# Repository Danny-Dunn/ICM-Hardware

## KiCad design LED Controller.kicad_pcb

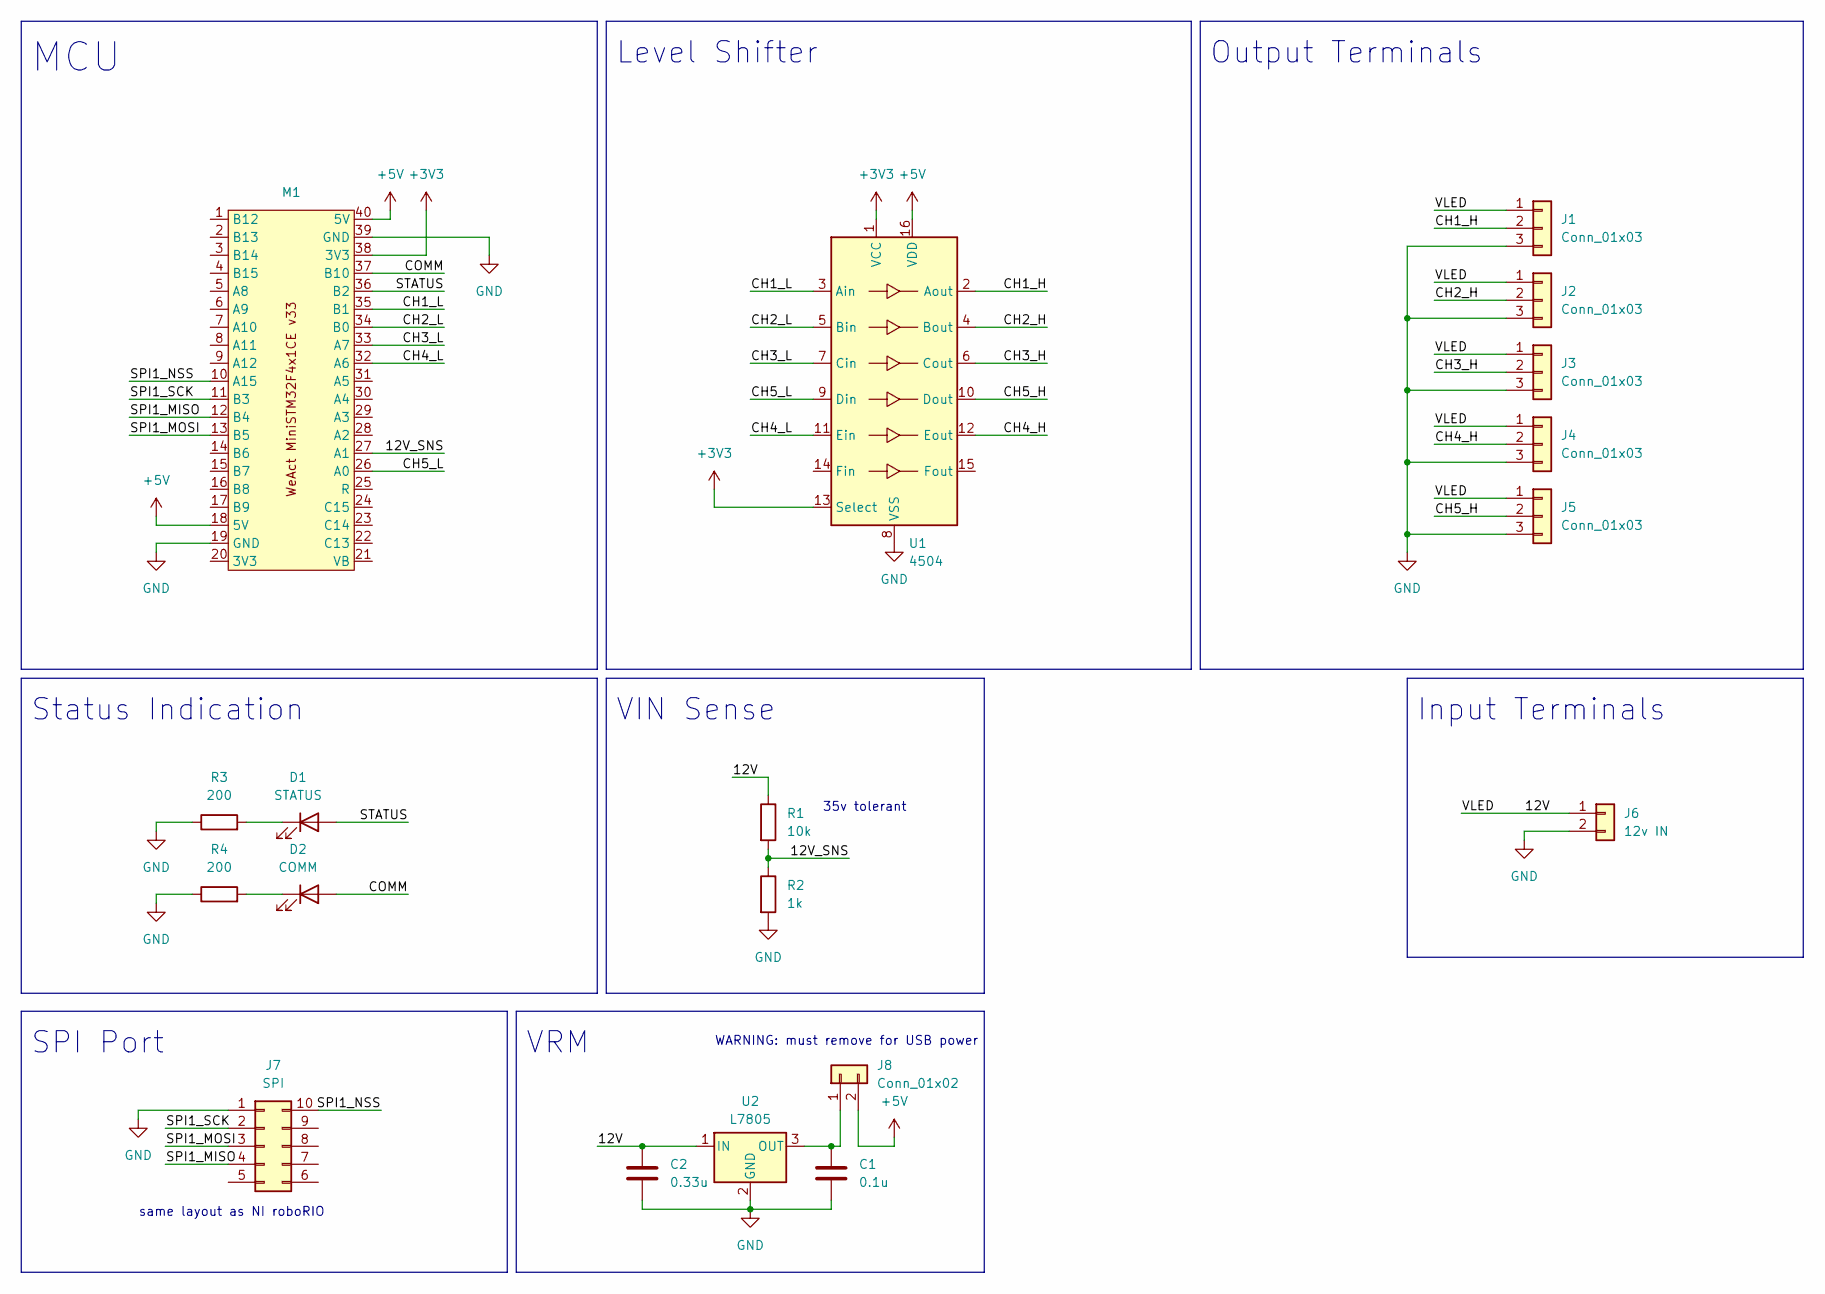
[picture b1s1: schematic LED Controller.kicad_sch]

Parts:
C1: 0.1u; CP_Radial_D5.0mm_P2.00mm
C2: 0.33u; CP_Radial_D4.0mm_P1.50mm
D1: STATUS; LED_0805_2012Metric
D2: COMM; LED_0805_2012Metric
J1, J2, J3, J4, J5: Conn_01x03; PinHeader_1x03_P2.54mm_Vertical
J6: 12v IN; TerminalBlock_WAGO_804-102_1x02_P5.00mm_45Degree
J7: SPI; PinHeader_2x05_P2.54mm_Vertical
J8: Conn_01x02; PinHeader_1x02_P2.54mm_Vertical
M1: MiniSTM32F4x1CE
R1: 10k; R_0805_2012Metric
R2: 1k; R_0805_2012Metric
R3, R4: 200; R_0805_2012Metric
U1: 4504; DIP-16_W7.62mm
U2: L7805; TO-220-3_Horizontal_TabDown

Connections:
+3V3: M1.38 (3V3), U1.1 (VCC), U1.13 (Select)
+5V: J8.2, M1.18 (5V), M1.40 (5V), U1.16 (VDD)
/12V: C2.1, J1.1, J2.1, J3.1, J4.1, J5.1, J6.1, R1.1, U2.1 (IN)
/12V_SNS: M1.27 (A1), R1.2, R2.1
/CH1_H: J1.2, U1.2 (Aout)
/CH1_L: M1.35 (B1), U1.3 (Ain)
/CH2_H: J2.2, U1.4 (Bout)
/CH2_L: M1.34 (B0), U1.5 (Bin)
/CH3_H: J3.2, U1.6 (Cout)
/CH3_L: M1.33 (A7), U1.7 (Cin)
/CH4_H: J4.2, U1.12 (Eout)
/CH4_L: M1.32 (A6), U1.11 (Ein)
/CH5_H: J5.2, U1.10 (Dout)
/CH5_L: M1.26 (A0), U1.9 (Din)
/COMM: D2.2 (A), M1.37 (B10)
/SPI1_MISO: J7.4, M1.12 (B4)
/SPI1_MOSI: J7.3, M1.13 (B5)
/SPI1_NSS: J7.10, M1.10 (A15)
/SPI1_SCK: J7.2, M1.11 (B3)
/STATUS: D1.2 (A), M1.36 (B2)
GND: C1.2, C2.2, J1.3, J2.3, J3.3, J4.3, J5.3, J6.2, J7.1, M1.19 (GND), M1.39 (GND), R2.2, R3.1, R4.1, U1.8 (VSS), U2.2 (GND)
unnamed: D1.1 (K), R3.2
unnamed: D2.1 (K), R4.2
unnamed: C1.1, J8.1, U2.3 (OUT)

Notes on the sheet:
Input Terminals
Level Shifter
Status Indication
same layout as NI roboRIO
VRM
SPI Port
WARNING: must remove for USB power
35v tolerant
MCU
Output Terminals
VIN Sense

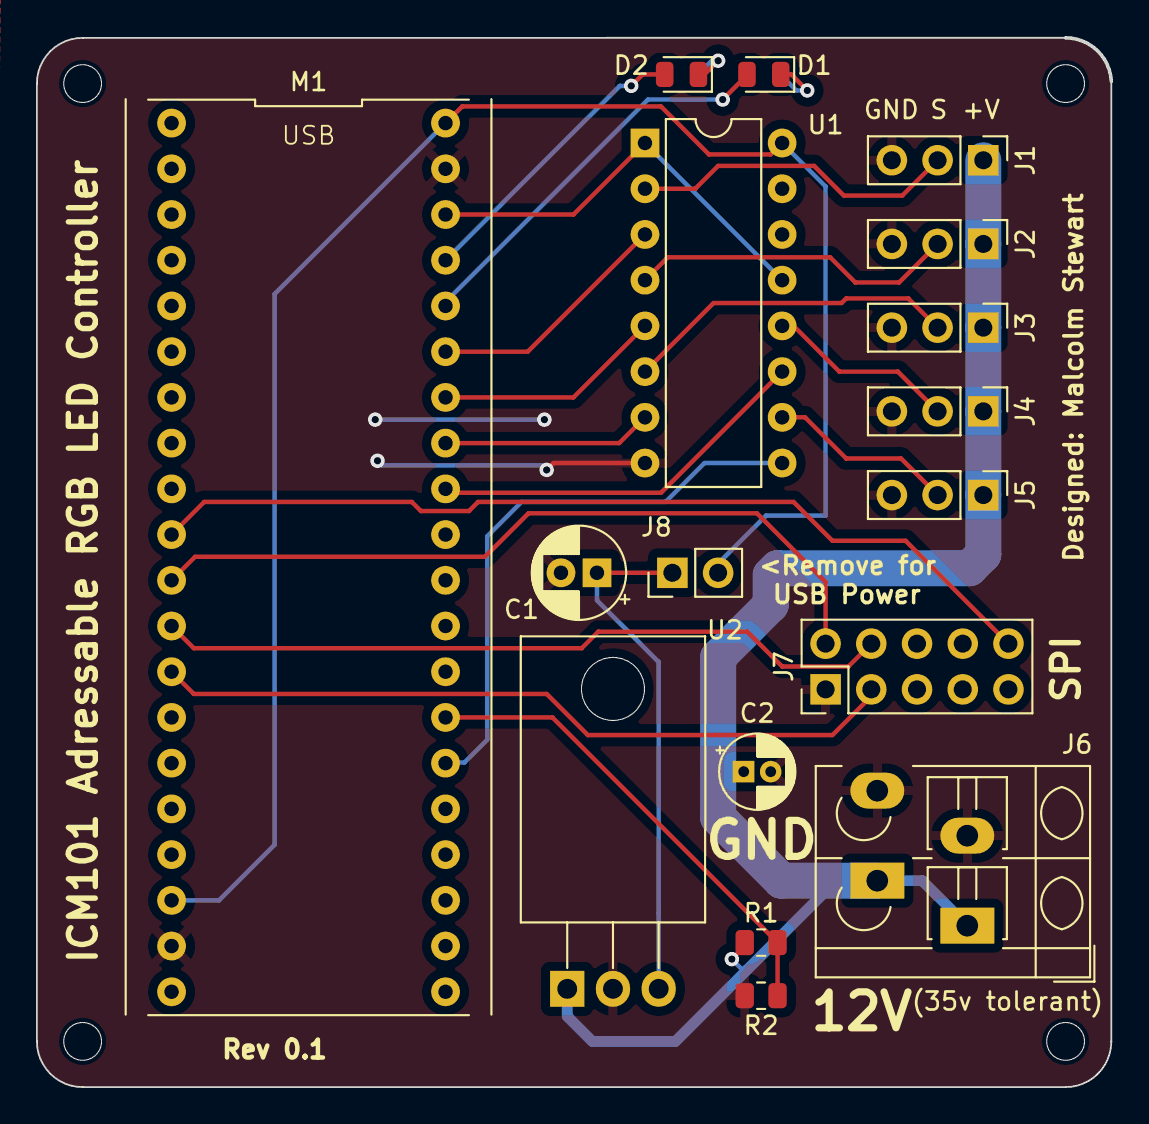
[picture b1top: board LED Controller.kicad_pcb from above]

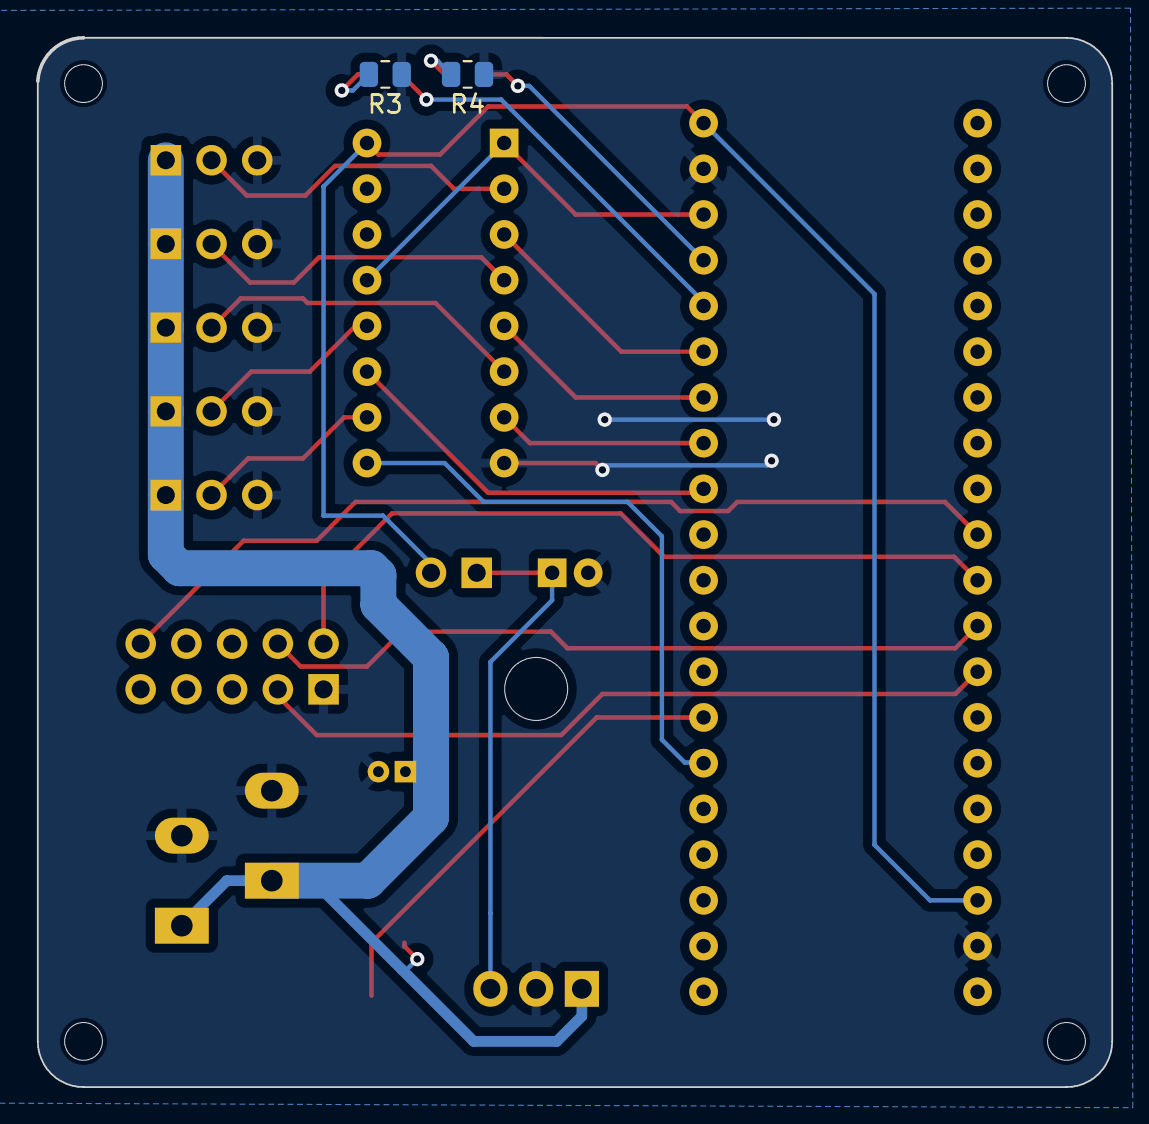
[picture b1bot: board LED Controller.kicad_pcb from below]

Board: 2 copper layers, 59.6 x 58.2 mm, 23 parts (2 on the bottom side), 24 nets.

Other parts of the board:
H1, H2, H3, H4: MountingHole_2.1mm

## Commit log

2024-02-27 Add project files
2025-07-04 Add export
